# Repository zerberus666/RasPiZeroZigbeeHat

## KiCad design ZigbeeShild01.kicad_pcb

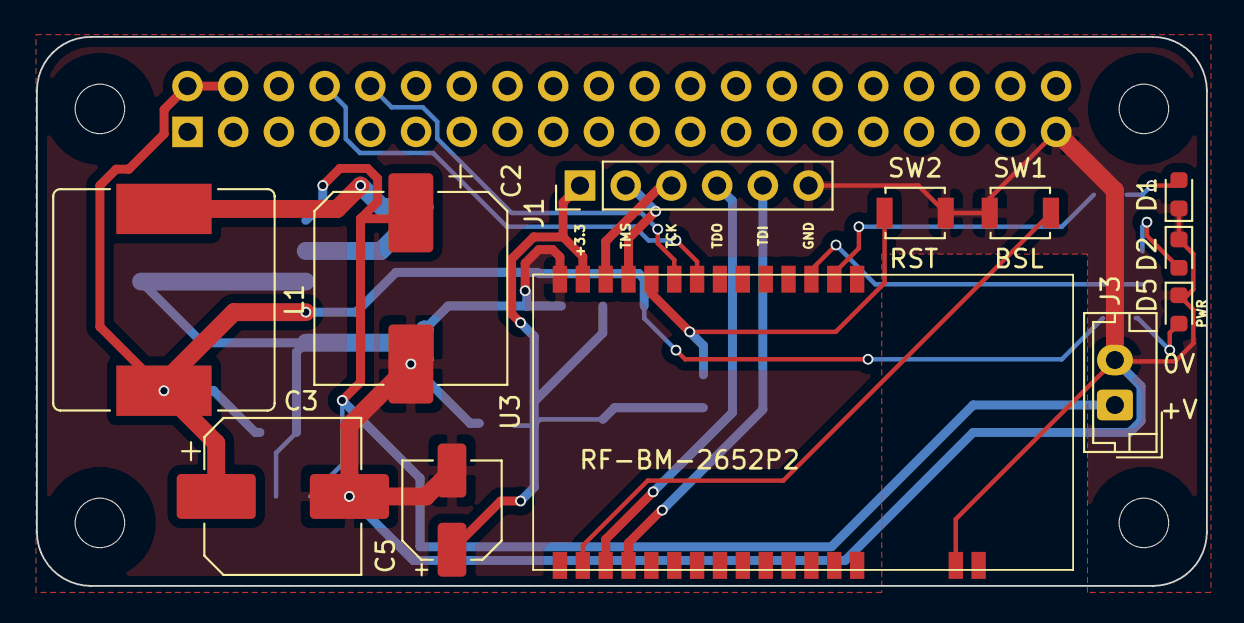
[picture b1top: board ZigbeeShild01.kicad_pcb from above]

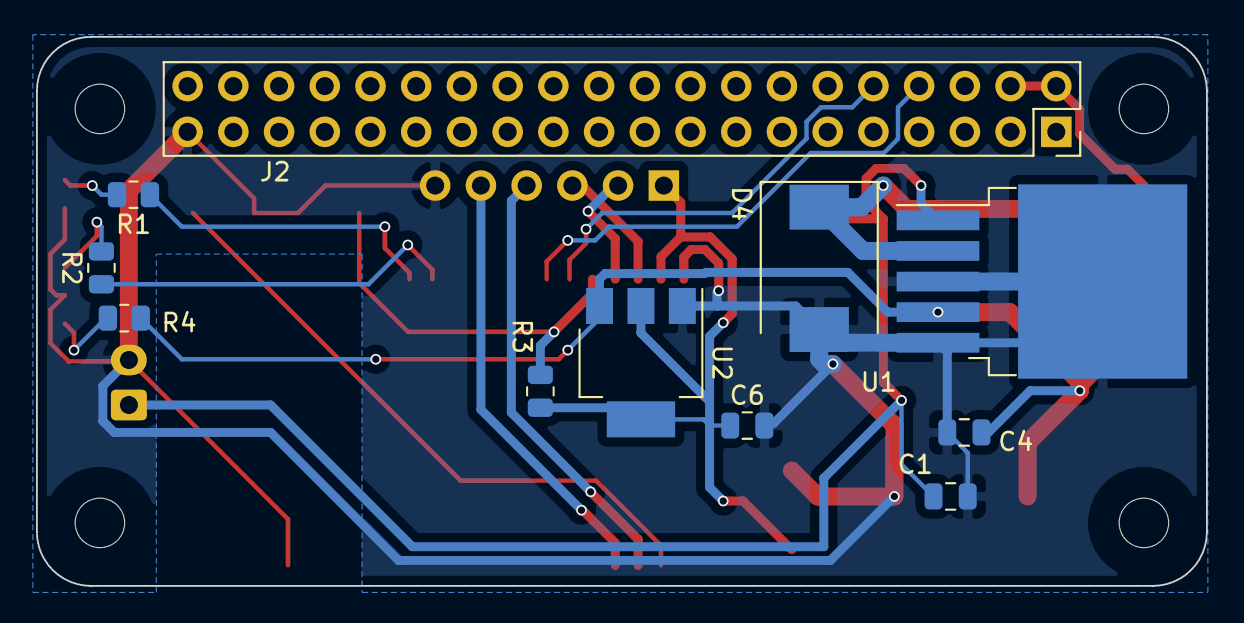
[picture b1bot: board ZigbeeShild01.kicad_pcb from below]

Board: 2 copper layers, 65.0 x 30.5 mm, 23 parts (11 on the bottom side), 18 nets.

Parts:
C1, C4: 100p; C_0805_2012Metric
C2: 100uF_50V; CP_Elec_10x10.5
C3: 220uF_35V; CP_Elec_8x10.5
C5: 22u; CP_Elec_5x5.4
C6: 0.1u; C_0805_2012Metric
D1, D2, D5: LED; LED_0603_1608Metric
D4: B340; D_SMC
J1: Conn_01x06_Male; PinHeader_1x06_P2.54mm_Vertical
J2: RPi_GPIO; PinSocket_2x20_P2.54mm_Vertical
J3: Power; JST_EH_B2B-EH-A_1x02_P2.50mm_Vertical
L1: 68uH; L_Bourns_SRR1210A
R1, R2, R4: 1k; R_0805_2012Metric
R3: 10k; R_0805_2012Metric
SW1: BSL; SW_SPST_B3U-1000P
SW2: RST; SW_SPST_B3U-1000P
U1: LM2596S-5; TO-263-5_TabPin3
U2: AMS1117-3.3; SOT-223-3_TabPin2
U3: RF-BM-2652P2; RF-BM-2652

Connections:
+3V3: C5.1, C6.1, J1.1, R3.2, U2.2, U3.13
+5V: C3.1, C4.1, J2.2, J2.4, L1.2, R4.1, U1.4, U2.3
GND: C1.2, C2.2, C3.2, C4.2, C5.2, C6.2, D1.1, D2.1, D4.2, D5.1, J1.6, J2.39, J3.2, SW1.1, SW2.2, U1.3, U1.5, U2.1, U3.14, U3.29
unnamed: C1.1, C2.1, J3.1, U1.1
unnamed: D1.2, R1.2
unnamed: D2.2, R2.2
unnamed: D4.1, L1.1, U1.2
unnamed: D5.2, R4.2
unnamed: R1.1, U3.2
unnamed: R2.1, U3.3
unnamed: R3.1, SW2.1, U3.10
unnamed: SW1.2, U3.16
Pi_RX: J2.10, U3.9
Pi_TX: J2.8, U3.8
TCK: J1.3, U3.12
TDI: J1.5, U3.18
TDO: J1.4, U3.17
TMS: J1.2, U3.11

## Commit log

2021-08-25 Gerber Files for production added
2021-08-26 some small changes in PCB
2021-09-02 BOM and Gerber files generated
2021-11-02 some changes
